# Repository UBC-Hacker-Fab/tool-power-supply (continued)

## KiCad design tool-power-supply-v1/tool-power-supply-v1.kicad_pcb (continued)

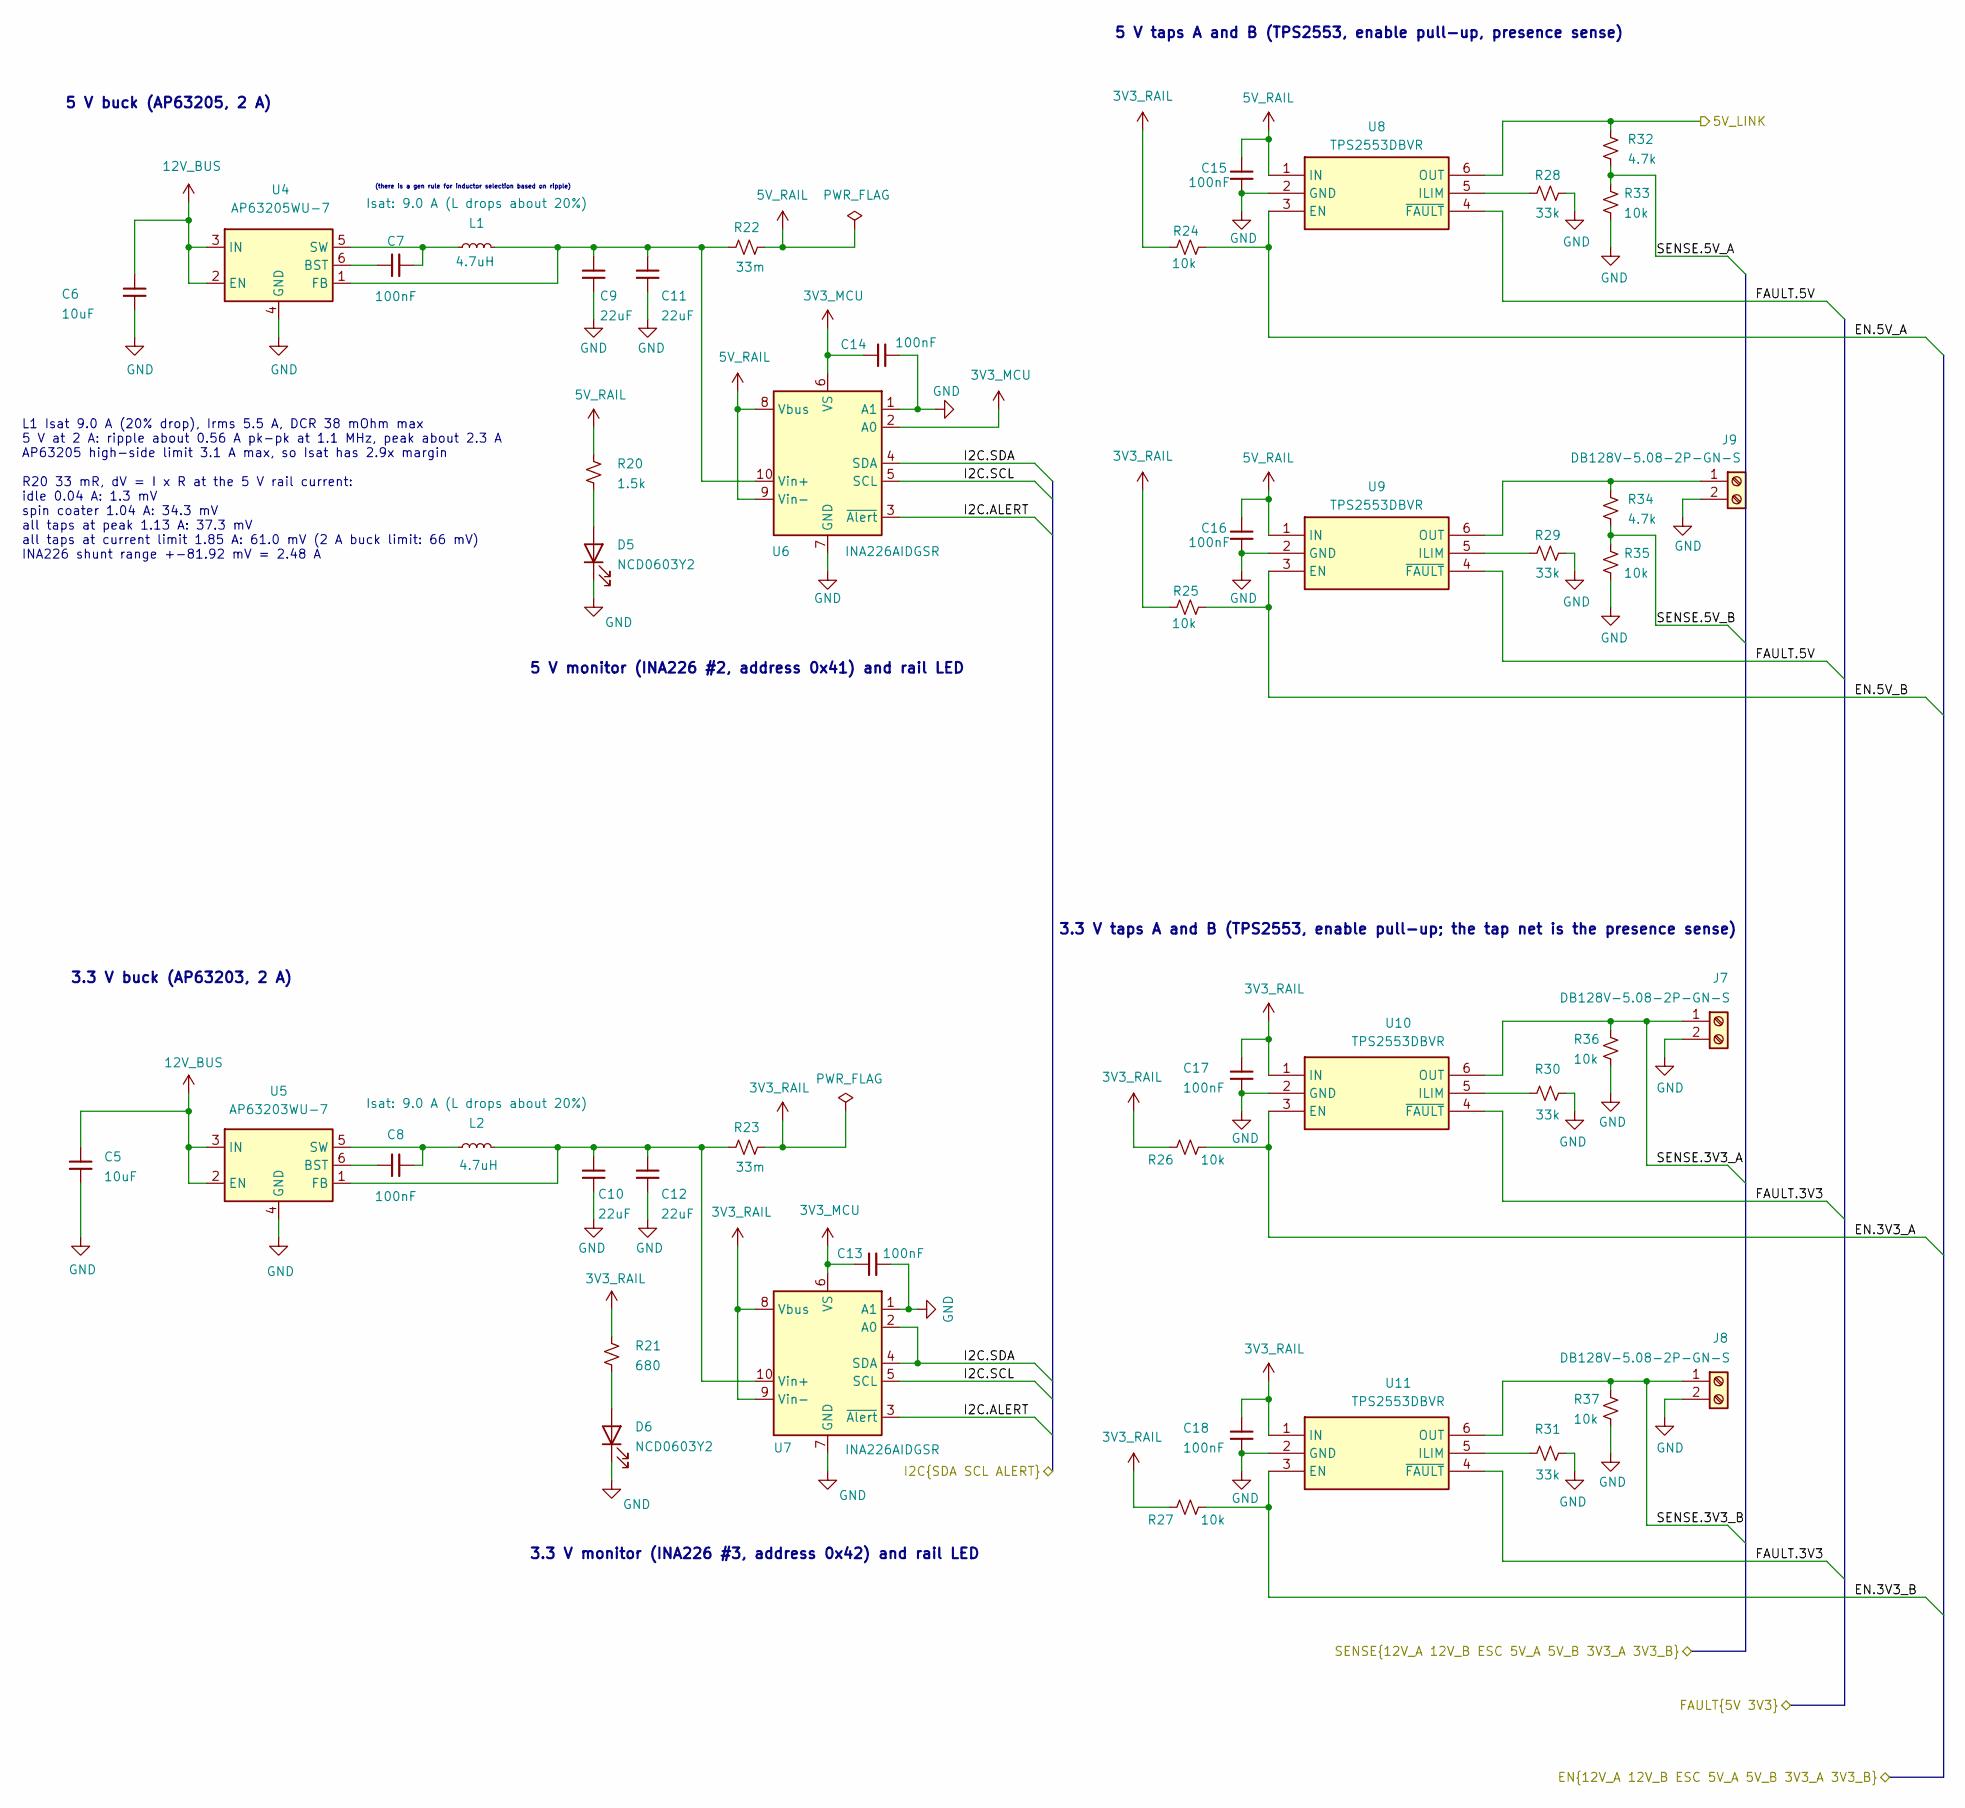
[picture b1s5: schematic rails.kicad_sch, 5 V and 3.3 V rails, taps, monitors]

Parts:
C5, C6: 10uF; C_1206_3216Metric; Voltage 50V; MPN CL31A106KBHNNNE; LCSC C13585
C7, C8: 100nF; C_0603_1608Metric; Voltage 50V; LCSC C14663
C9, C10, C11, C12: 22uF; C_0805_2012Metric; Voltage 25V; MPN CL21A226MAQNNNE; LCSC C45783
C13, C14, C15, C16, C17, C18: 100nF; C_0603_1608Metric; Voltage 50V; MPN CC0603KRX7R9BB104; LCSC C14663
D5, D6: NCD0603Y2; LED_0603_1608Metric; MPN NCD0603Y2; LCSC C89811
J7, J8, J9: DB128V-5.08-2P-GN-S; TerminalBlock_CUI_TB007-508-02_1x02_P5.08mm_Horizontal; MPN DB128V-5.08-2P-GN-S; LCSC C2915639
L1, L2: 4.7uH; L_Sumida_CDMC6D28_7.25x6.5mm; MPN SLO0630H4R7MTT; LCSC C207840
R20: 1.5k; R_0603_1608Metric; Tolerance 1%; MPN 0603WAF1501T5E; LCSC C22843
R21: 680; R_0603_1608Metric; Tolerance 1%; MPN 0603WAF6800T5E; LCSC C23228
R22, R23: 33m; R_1206_3216Metric; Tolerance 1%; MPN RLS12FTCR033; LCSC C912764
R24, R25, R26, R27, R33, R35, R36, R37: 10k; R_0603_1608Metric; Tolerance 1%; MPN 0603WAF1002T5E; LCSC C25804
R28, R29, R30, R31: 33k; R_0603_1608Metric; Tolerance 1%; MPN 0603WAF3302T5E; LCSC C4216
R32, R34: 4.7k; R_0603_1608Metric; Tolerance 1%; MPN 0603WAF4701T5E; LCSC C23162
U4: AP63205WU-7; TSOT-23-6; MPN AP63205WU-7; LCSC C2071056
U5: AP63203WU-7; TSOT-23-6; MPN AP63203WU-7; LCSC C780769
U6, U7: INA226AIDGSR; MSOP-10_3x3mm_P0.5mm; MPN INA226AIDGSR; LCSC C49851
U8, U9, U10, U11: TPS2553DBVR; SOT95P280X145-6N; MPN TPS2553DBVR; LCSC C55266

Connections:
3V3_MCU: C13.1, C14.1, U6.2 (A0), U6.6 (VS), U7.6 (VS); also elsewhere on the board
5V_RAIL: C15.1, C16.1, R20.1, R22.2, U6.8 (Vbus), U6.9 (Vin-), U8.1 (IN), U9.1 (IN); also elsewhere on the board
12V_BUS: C5.1, C6.1, U4.2 (EN), U4.3 (IN), U5.2 (EN), U5.3 (IN); also elsewhere on the board
/bus12v/EN.3V3_A: R26.1, U10.3 (EN); also elsewhere on the board
/bus12v/EN.3V3_B: R27.1, U11.3 (EN); also elsewhere on the board
/bus12v/EN.5V_A: R24.1, U8.3 (EN); also elsewhere on the board
/bus12v/EN.5V_B: R25.1, U9.3 (EN); also elsewhere on the board
/bus12v/I2C.ALERT: U6.3 (~Alert), U7.3 (~Alert); also elsewhere on the board
/bus12v/I2C.SCL: U6.5 (SCL), U7.5 (SCL); also elsewhere on the board
/bus12v/I2C.SDA: U6.4 (SDA), U7.2 (A0), U7.4 (SDA); also elsewhere on the board
/bus12v/SENSE.3V3_A: J7.1, R36.1, U10.6 (OUT); also elsewhere on the board
/bus12v/SENSE.3V3_B: J8.1, R37.1, U11.6 (OUT); also elsewhere on the board
/bus12v/SENSE.5V_A: R32.2, R33.1; also elsewhere on the board
/bus12v/SENSE.5V_B: R34.2, R35.1; also elsewhere on the board
/mcu/5V_LINK: R32.1, U8.6 (OUT); also elsewhere on the board
/mcu/FAULT.3V3: U10.4 (~FAULT), U11.4 (~FAULT); also elsewhere on the board
/mcu/FAULT.5V: U8.4 (~FAULT), U9.4 (~FAULT); also elsewhere on the board
GND: C5.2, C6.2, C9.2, C10.2, C11.2, C12.2, C13.2, C14.2, C15.2, C16.2, C17.2, C18.2, D5.1 (K), D6.1 (K), J7.2, J8.2, J9.2, R28.2, R29.2, R30.2, R31.2, R33.2, R35.2, R36.2, R37.2, U4.4 (GND), U5.4 (GND), U6.1 (A1), U6.7 (GND), U7.1 (A1), U7.7 (GND), U8.2 (GND), U9.2 (GND), U10.2 (GND), U11.2 (GND); also elsewhere on the board
unnamed: D5.2 (A), R20.2
unnamed: D6.2 (A), R21.2
unnamed: J9.1, R34.1, U9.6 (OUT)
unnamed: C7.1, U4.6 (BST)
unnamed: C9.1, C11.1, L1.2, R22.1, U4.1 (FB), U6.10 (Vin+)
unnamed: C7.2, L1.1, U4.5 (SW)
unnamed: C8.1, U5.6 (BST)
unnamed: C10.1, C12.1, L2.2, R23.1, U5.1 (FB), U7.10 (Vin+)
unnamed: C8.2, L2.1, U5.5 (SW)
unnamed: R28.1, U8.5 (ILIM)
unnamed: R29.1, U9.5 (ILIM)
unnamed: R30.1, U10.5 (ILIM)
unnamed: R31.1, U11.5 (ILIM)

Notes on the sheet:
5 V buck (AP63205, 2 A)
L1 Isat 9.0 A (20% drop), Irms 5.5 A, DCR 38 mOhm max 5 V at 2 A: ripple about 0.56 A pk-pk at 1.1 MHz, peak about 2.3 A AP63205 high-side limit 3.1 A max, so Isat has 2.9x margin R20 33 mR, dV = I x R at the 5 V rail current: idle 0.04 A: 1.3 mV spin coater 1.04 A: 34.3 mV all taps at peak 1.13 A: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
3.3 V taps A and B (TPS2553, enable pull-up; the tap net is the presence sense)
5 V monitor (INA226 #2, address 0x41) and rail LED
3.3 V monitor (INA226 #3, address 0x42) and rail LED
3.3 V buck (AP63203, 2 A)
(there is a gen rule for inductor selection based on ripple)
5 V taps A and B (TPS2553, enable pull-up, presence sense)

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
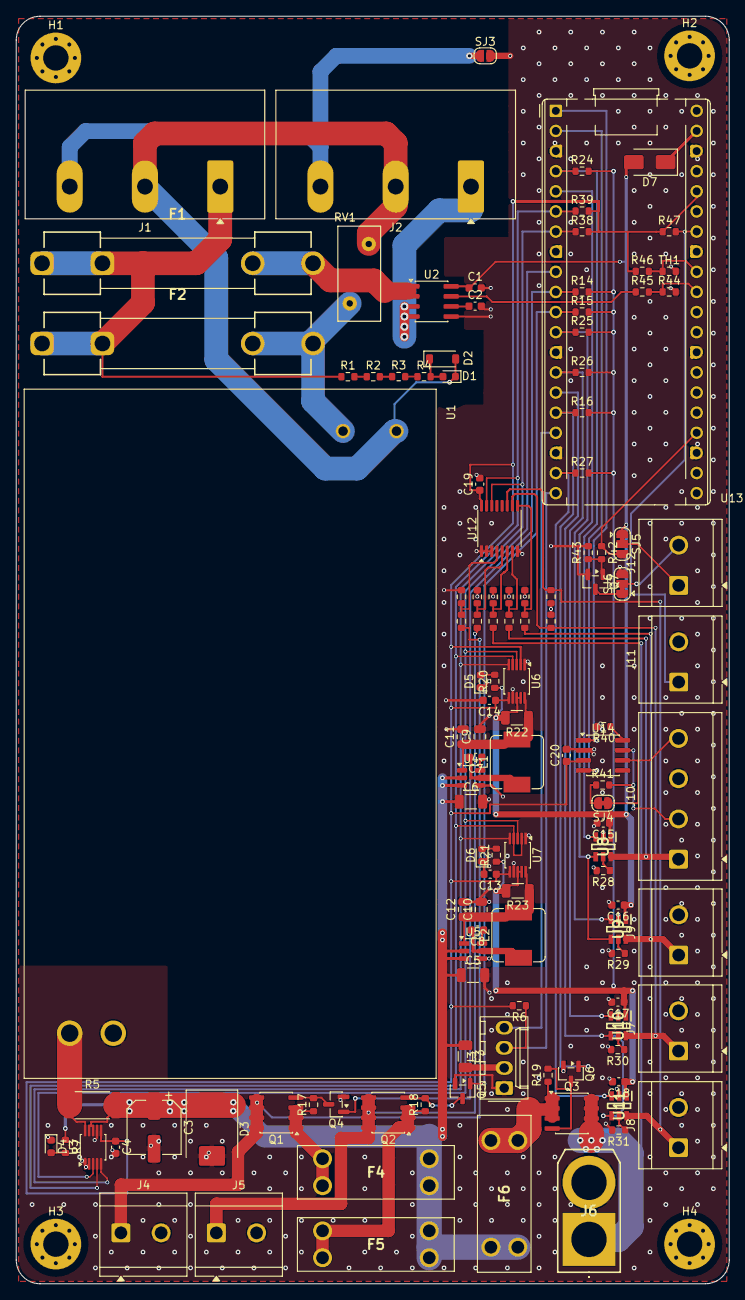
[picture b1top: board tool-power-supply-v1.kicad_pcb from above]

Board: 4 copper layers, 90.0 x 160.0 mm, 125 parts (0 on the bottom side), 79 nets.
